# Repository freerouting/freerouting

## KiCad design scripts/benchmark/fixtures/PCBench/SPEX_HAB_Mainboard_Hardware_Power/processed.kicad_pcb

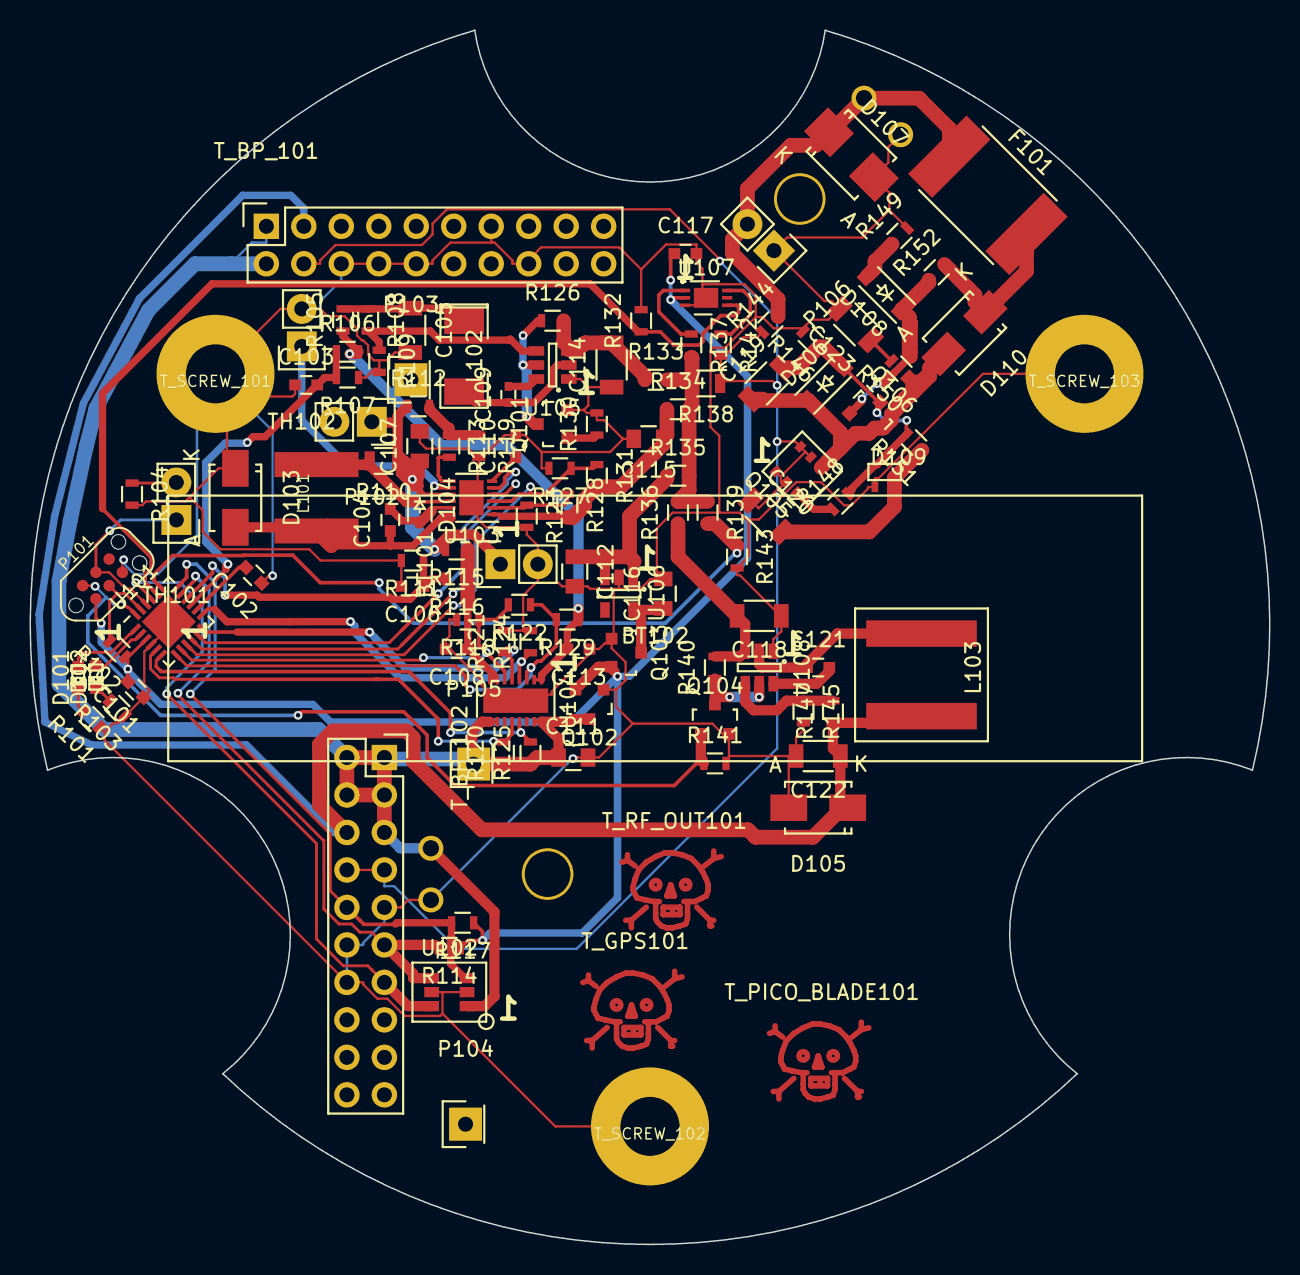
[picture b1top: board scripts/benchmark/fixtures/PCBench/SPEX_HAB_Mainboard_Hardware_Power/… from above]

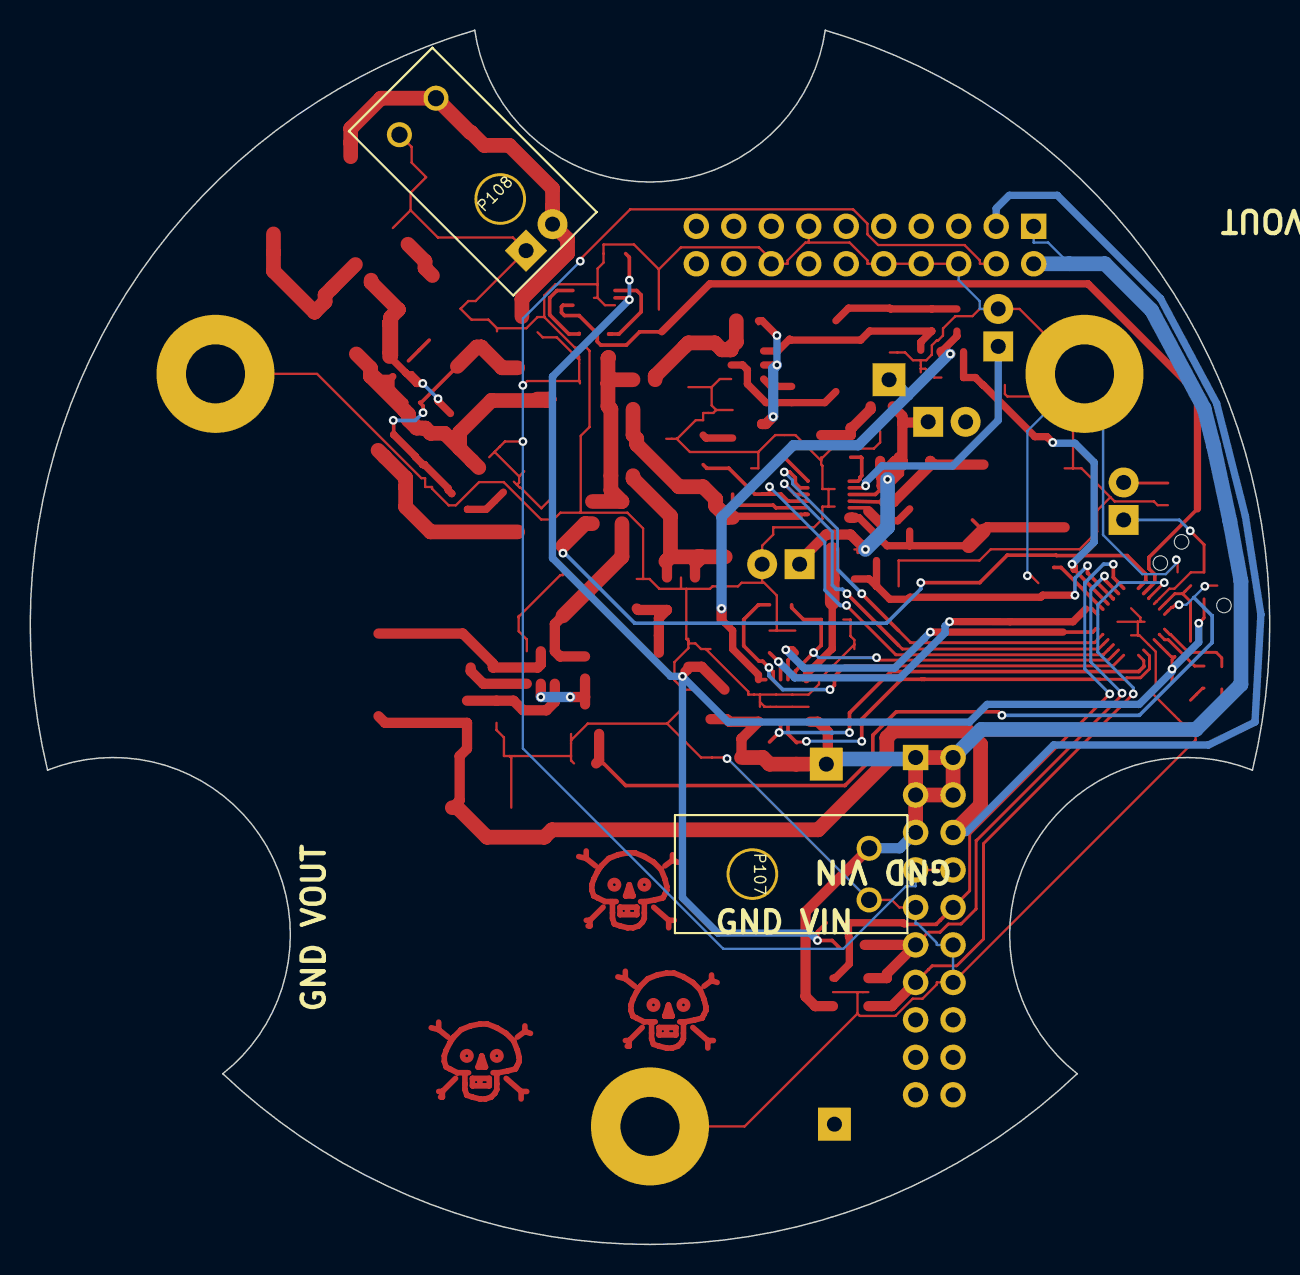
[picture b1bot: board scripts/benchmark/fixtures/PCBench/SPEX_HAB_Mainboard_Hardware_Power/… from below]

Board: 2 copper layers, 84.0 x 82.3 mm, 123 parts (2 on the bottom side), 68 nets.

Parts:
BT101: BATTERY; Pin_Header_Straight_1x02
BT102: 18650Outline; 18650
C101, C102, C104, C117: 1uf; C_0603
C103, C106: DNP; C_0603
C105, C122: 47uf; C_1206
C107, C115, C116: 10uf; C_0805
C108, C113: 1u; C_0603
C109: 100nf; C_0402
C110: .68uf; C_0603
C111: 4.7uf; C_0805
C112: 10u; C_0805
C114, C118: 22uf; C_1206
C119, C123: 1uf 100v; C_1206
C120: .1uf 100v; C_1206
C121: 100nf; C_0603
D101, D102: LED; LED-0603
D103: CMSH3-40MA; Diode-SMA_Standard
D104: CMDSH2-4L; SOD-323
D105: ZENER; Diode-SMA_Standard
D106, D108: ZENER; SOD-123
D107: ZENER; Diode-SMB_Standard
D109: D_Schottky_x2_Serial_AKC; sc70
D110: DIODE; Diode-SMA_Standard
F101: FUSE; Fuse_SMD2920
L101: 5.6uh; ASPI-6045S-5R6M-T
L102: 2.2uh; SMD-2010_Pol
L103: 3.3uh; NRS8030T3R3MJGJ
P101: TC2030-CTX; TC2030-NL_SMALL
P102: BAT_POS; Socket_Strip_Straight_1x02
P103: 3v3Out; Socket_Strip_Straight_1x01
P104: BAT_NEG; Socket_Strip_Straight_1x01
P105: 3v3Bypass; Socket_Strip_Straight_1x01
P106: 12Vin; Pin_Header_Straight_1x02
P107: 3v3Vout; ultraFitCONN_2
P108: 12Vin2; ultraFitCONN_2
Q101, Q104: MOS_N_numbered; SOT-23
Q102, Q103: Q_PMOS_GSD; SOT-23
Q105: Si3407DV
Q106: Q_PNP_BEC; SOT-23
R101, R103: 80; R_0603
R102, R143: 10000; R_0603
R104: 1500; R_0603
R105, R115, R133, R134, R135, R136: 0; R_0603
R106, R116: 3.9K; R_0603
R107, R111: 1K; R_0603
R108, R146: 33.2k; R_0603
R109, R123, R127, R145: 10k; R_0603
R110: 0.1; R_0805
R112: 14.3k; R_0603
R113: 237k; R_0603
R114, R117: 4.7k; R_0603
R118: 95.3K; R_0603
R119: 330k; R_0603
R120, R125: 470K; R_0603
R121, R124: 165; R_0603
R122: 30.1K; R_0603
R126, R130, R140, R141: 10K; R_0603
R128: 13.7k; R_0603
R129: 237K; R_0603
R131: 49.9K; R_0603
R132: 1000; R_0603
R137, R142: 100; R_0603
R138: 0.02; R_0805
R139: 200000; R_0603
R144: DNP; R_0603
R147: 56.2k; R_0603
R148, R150: 10; R_0603
R149: 27.4k; R_0603
R151: 10.2k; R_0603
R152: 100k; R_0603
TH101, TH102: THERMISTOR; Pin_Header_Straight_1x02
T_BP_101, T_BP_102: CONN_02X10; Socket_Strip_Straight_2x10
T_GPS101: SMA; Symbol_Danger_CopperTop_Small
T_PICO_BLADE101: CONN_01X08; Symbol_Danger_CopperTop_Small
T_RF_OUT101: SMA; Symbol_Danger_CopperTop_Small
T_SCREW_101, T_SCREW_102, T_SCREW_103: CONN_01X01; mounting_screw
U101: KL03-QFN24; QFN-24-1EP_4x4mm_Pitch0.5mm
U102: MMQA; SC-74
U103: LT3652; DFN-12-1EP_3x3mm_Pitch0.45mm
U104: LT4415; DFN-16-1EP_3x5mm_Pitch0.5mm
U105, U108: TPS563200; SOT-23-6
U106: TLV71209DBV; SOT-23-5
U107: LT6105

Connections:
/12Vto3v3/En: Q101.1, R130.1
/12Vto3v3/Vin: C114.2, R126.2, R133.1, U105.3
/12Vto3v3/Vout: C105.1, L102.1, R105.2, R108.1
/12Vto5V/En: P101.2, Q104.1, R141.1, U101.24
/12Vto5V/Vin: C118.2, R136.1, R140.2, U108.3
/BatVOut: C106.1, R111.1, R116.2, U101.16
/MainCurrent: R132.1, U101.20, U107.4
/SWD_CLK: P101.4, TH101.1, U101.22
/SWD_RST: P101.3, R102.2, U101.23
/SwitchVOut: C103.2, R106.1, R107.2, U101.15
/VBackup: C101.2, C117.1, P101.1, Q102.2, Q103.2, R102.1, R114.1, R117.1, U101.3, U107.2
/VInSense: R139.2, R143.1, U101.19
/VREF: C102.2, U101.14
/dualIdealDiode/Current1: R124.1, U101.13, U104.4
/dualIdealDiode/Current2: R121.1, U101.12, U104.5
/dualIdealDiode/EN1: R122.1, R129.2, U101.7, U104.3
/dualIdealDiode/EN2: R118.1, R122.2, U101.8, U104.6
/dualIdealDiode/VIN1: C113.2, P103.1, R105.1, R106.2, R129.1, U104.1, U104.2
/dualIdealDiode/VIN2: C108.1, R115.1, R116.1, U104.7, U104.8
/dualIdealDiode/WARN1: R125.2, U101.6, U104.13
/dualIdealDiode/WARN2: R120.2, U101.5, U104.12
/lifepo4Charger/CHRG: U101.10, U103.4
/lifepo4Charger/FAULT: U101.11, U103.5
/lifepo4Charger/SHDN: R127.1, R131.1, U101.9, U103.3
/lifepo4Charger/Vin: C115.1, R128.2, R131.2, R134.1, U103.1
/lifepo4Charger/Vout: BT101.1, C107.1, D104.1, P102.1, R110.1, R112.1, R115.2, U103.9
/protection/Vin: D107.1, F101.1, P106.2, P108.2, R144.2
/template/3v3: C111.1, P105.1, P107.1, Q102.3, R120.1, R125.1, T_BP_101.1, T_BP_101.2, T_BP_102.1, T_BP_102.2, T_BP_102.3, T_BP_102.4, T_BP_102.5, U102.1, U104.9, U104.10, U104.15, U104.16
/template/5v: C122.1, D105.1, L103.1, R147.1, T_BP_101.3, T_BP_102.6
/template/PSU_IRQ: T_BP_102.13, U101.21, U102.6
/template/PSU_SCL: R114.2, T_BP_102.11, U101.17, U102.4
/template/PSU_SDA: R117.2, T_BP_102.10, U101.18, U102.3
/template/VBUS: C120.1, Q105.1, Q105.2, Q105.5, Q105.6, R138.1, R142.2, R144.1, T_BP_101.4, T_BP_102.7, T_BP_102.8
GND: BT101.2, C101.1, C102.1, C103.1, C105.2, C106.2, C107.2, C108.2, C110.2, C111.2, C112.2, C113.1, C114.1, C115.2, C116.2, C117.2, C118.1, C122.2, C123.2, D103.1, D105.2, D107.2, D109.1, P101.5, P106.1, P107.2, P108.1, Q101.2, Q102.1, Q103.1, Q104.2, R101.1, R103.1, R104.2, R107.1, R109.2, R111.2, R118.2, R119.2, R121.2, R123.2, R124.2, R127.2, R130.2, R132.2, R141.2, R143.2, R145.2, R146.2, R149.2, TH102.2, T_BP_101.6, T_BP_101.8, T_BP_101.10, T_BP_101.13, T_BP_101.16, T_BP_102.9, T_BP_102.12, T_BP_102.14, T_SCREW_101.1, T_SCREW_102.1, T_SCREW_103.1, U101.4, U101.25, U102.2, U102.5, U103.13, U104.17, U105.1, U106.2, U107.3, U107.7, U108.1
unnamed: C123.1, R150.2
unnamed: C112.1, R135.1, U106.1, U106.3
unnamed: C116.1, Q103.3, U106.5
unnamed: C109.1, L102.2, U105.2
unnamed: C109.2, U105.6
unnamed: C110.1, U103.6
unnamed: C104.1, D103.2, L101.1, U103.12
unnamed: C104.2, D104.2, U103.11
unnamed: C119.1, D106.1, D110.2, Q105.4, Q106.2, R150.1
unnamed: C119.2, D106.2, D109.3, Q106.3, R146.1, R148.2, R151.2
unnamed: C120.2, D109.2, R151.1
unnamed: C121.1, L103.2, U108.2
unnamed: C121.2, U108.6
unnamed: D110.1, F101.2, R152.2
unnamed: D108.1, Q106.1, R152.1
unnamed: D108.2, R149.1
unnamed: D102.1, R103.2
unnamed: D102.2, U101.2
unnamed: D101.1, R101.2
unnamed: D101.2, U101.1
unnamed: L101.2, R110.2, U103.10
unnamed: Q105.3, R148.1
unnamed: Q101.3, R126.1, U105.5
unnamed: Q104.3, R140.1, U108.5
unnamed: R104.1, TH101.2
unnamed: R142.1, U107.6
unnamed: R137.1, U107.1
unnamed: R133.2, R134.2, R135.2, R136.2, R137.2, R138.2, R139.1
unnamed: R108.2, R109.1, U105.4
unnamed: R123.1, R128.1, U103.2
unnamed: R112.2, R113.1, R119.1
unnamed: R113.2, U103.7
unnamed: R145.1, R147.2, U108.4
unnamed: TH102.1, U103.8

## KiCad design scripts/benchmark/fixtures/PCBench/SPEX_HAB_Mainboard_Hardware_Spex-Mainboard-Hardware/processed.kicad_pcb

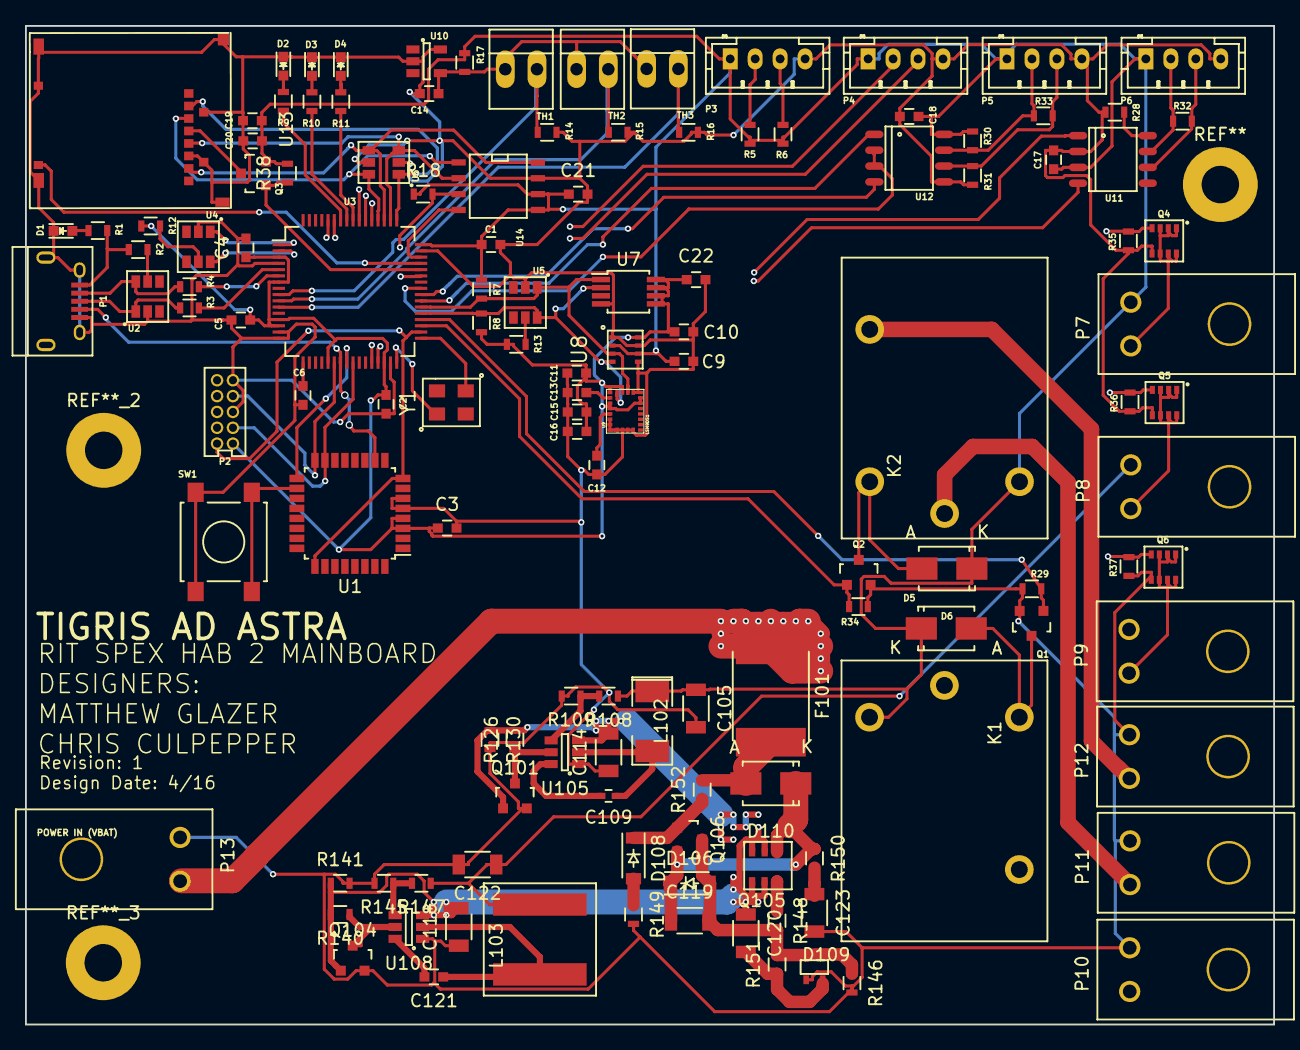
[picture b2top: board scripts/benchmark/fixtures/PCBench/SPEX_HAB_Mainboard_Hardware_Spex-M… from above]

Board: 4 copper layers, 100.0 x 80.0 mm, 131 parts (0 on the bottom side), 89 nets.

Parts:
C1, C2, C3, C4: 1uF; C_0603
C5: 2.2uF; C_0603
C6, C19: .1uF; C_0603
C9, C10, C17, C18, C21, C22: C; C_0603
C11, C13, C15: 100nF; C_0603
C12: 10nF; C_0603
C14: 4.7uF; C_0603
C16, C20: 10uF; C_0603
C105, C122: 47uf; C_1206
C109: 100nf; C_0402
C114, C118: 22uf; C_1206
C119, C123: 1uf 100v; C_1206
C120: .1uf 100v; C_1206
C121: 100nf; C_0603
D1, D2, D3, D4: LED; LED_0603
D5, D6: FM5819-W; SMA_Standard
D106, D108: ZENER; SOD-123
D109: D_Schottky_x2_Serial_AKC; sc70
D110: DIODE; Diode-SMA_Standard
F101: FUSE; Fuse_SMD2920
K1, K2: G5LE_1A4_DC3; G5LE-1A4-DC3
L102: 2.2uh; SMD-2010_Pol
L103: 3.3uh; NRS8030T3R3MJGJ
P1: USB_OTG; USB_Micro-B
P2: SWD Header; SWD-10
P3, P4, P5, P6: CONN_01X04; JST_PH_B4B-PH-K_04x2.00mm_Straight
P7, P8, P9, P10, P11, P12, P13: CONN_01X02; ultraFitCONN_2
Q1, Q2: 2N7002K; SOT-23
Q3: BSS215PH6327; SOT-23
Q4, Q5, Q6: Si5468DC; ChipFet-8
Q101, Q104: MOS_N_numbered; SOT-23
Q105: Si3407DV
Q106: Q_PNP_BEC; SOT-23
R1, R9, R10, R11: 1K; R_0603
R2, R12, R18, R29, R34, R38, R126, R130, R140, R141: 10K; R_0603
R3, R4: 33; R_0603
R5, R6, R7, R8: 4.7K; R_0603
R13, R30, R31, R35, R36, R37, R109, R145: 10k; R_0603
R14, R15, R16: 12k; R_0603
R17, R28: R; R_0603
R32, R33: 120; R_0603
R108, R146: 33.2k; R_0603
R147: 56.2k; R_0603
R148, R150: 10; R_0603
R149: 27.4k; R_0603
R151: 10.2k; R_0603
R152: 100k; R_0603
SW1: SW_PUSH; SW_SPST_B3S-1000
TH1, TH2, TH3: THERMISTOR; PINHEAD1-2
U1: MKL04Z32VLC4; LQFP-32_7x7mm_Pitch0.8mm
U2, U4, U5: NUP2201MR6; TSOP-6
U3: MK20DX256VLH7; LQFP-64_10x10mm_Pitch0.5mm
U6: MMQA6V2T1G; TSOP-6
U7: MCP9808T; MSOP-8_3x3mm_Pitch0.65mm
U8: BME280; LGA-8
U9: LSM9DS1; LGA-24
U10: LM4030; SOT-23-5
U11: MCP2551-I/SN; SO-8
U12: ST1480ABDR; SO-8
U13: SCHA4B0419; SCH4B0419
U14: AT45DB641E; SOIC-8-N
U105, U108: TPS563200; SOT-23-6
Y1: Crystal; CX3225GB16000D0HPQCC

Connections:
3.3V_MOS_CTRL: Q4.4, R35.2, U3.55
5V_MOS_CTRL: Q5.4, R36.2, U3.54
+3V3: C1.1, C2.1, C3.1, C4.1, C5.1, C9.1, C10.1, C11.1, C15.1, C16.1, C17.1, C18.1, C19.1, C20.1, C21.1, C22.1, C105.1, D5.1, D6.1, K1.4, K2.4, L102.1, P2.1, P3.1, P4.1, P5.1, P6.1, P7.2, Q3.2, R5.2, R6.2, R7.2, R8.2, R12.1, R13.1, R17.1, R18.1, R30.1, R38.2, R108.1, U1.3, U1.4, U3.3, U3.7, U3.13, U3.14, U3.21, U3.30, U3.48, U7.5, U7.6, U7.7, U7.8, U8.2, U8.6, U8.8, U9.1, U9.3, U9.7, U9.8, U9.22, U9.23, U11.3, U12.8, U14.5, U14.6
+5V: C122.1, L103.1, P8.2, R147.1
/Data_Input_Output/3.3V_MOS_OUT: P7.1, Q4.1, Q4.2, Q4.3, Q4.6, Q4.7, Q4.8
/Data_Input_Output/5V_MOS_OUT: P8.1, Q5.1, Q5.2, Q5.3, Q5.6, Q5.7, Q5.8
/Data_Input_Output/Battery_Out: K1.3, P10.1
/Data_Input_Output/CANH_out: P6.2, R32.1, U11.7
/Data_Input_Output/CANL_out: P6.3, R32.2, U11.6
/Data_Input_Output/RS485_A: P5.3, R31.1, R33.2, U12.6
/Data_Input_Output/RS485_B: P5.2, R30.2, R33.1, U12.7
/Data_Input_Output/User_In: K2.1, P11.1
/Data_Input_Output/User_Out: K2.3, P12.1
/Data_Input_Output/Vbus_MOS_OUT: P9.1, Q6.1, Q6.2, Q6.3, Q6.6, Q6.7, Q6.8
/HAB Sensors/2.5VRefVoltage: C14.1, R17.2, TH1.1, TH2.1, TH3.1, U10.4
/PTA6: P1.4, U1.10, U3.23
/PTA7: P2.2, U1.15, U3.25
/PTB0: P2.4, U1.16, U3.22
/PTB1: U1.17, U3.24
/PTB2: SW1.1, U1.18
CAN0_RX: U3.29, U11.4
CAN0_TX: U3.28, U11.1
Flash_Reset: R18.2, U3.43, U14.3
GND: C1.2, C2.2, C3.2, C4.2, C5.2, C6.2, C9.2, C10.2, C11.2, C12.2, C13.2, C14.2, C15.2, C16.2, C17.2, C18.2, C19.2, C20.2, C21.2, C22.2, C105.2, C114.1, C118.1, C122.2, C123.2, D1.1, D2.1, D3.1, D4.1, D109.1, P1.5, P1.6, P2.3, P2.5, P3.4, P4.4, P5.4, P6.4, P10.2, P11.2, P12.2, P13.1, Q1.2, Q2.2, Q4.5, Q5.5, Q6.5, Q101.2, Q104.2, R14.2, R15.2, R16.2, R28.2, R29.2, R31.2, R34.2, R35.1, R36.1, R37.1, R109.2, R130.2, R141.2, R145.2, R146.2, R149.2, SW1.2, U1.5, U1.6, U2.2, U3.4, U3.15, U3.16, U3.31, U3.47, U4.2, U5.2, U6.2, U6.5, U7.4, U8.1, U8.5, U8.7, U9.5, U9.6, U9.14, U9.15, U9.16, U9.17, U9.18, U9.19, U9.20, U10.2, U10.5, U11.2, U12.5, U13.6, U13.10, U14.7, U105.1, U108.1
I2C0_SCL: R8.1, U3.37, U5.6, U7.2, U8.4, U9.2
I2C0_SDA: R7.1, U3.38, U5.1, U7.1, U8.3, U9.4
I2C1_SCL: P3.3, R6.1, U3.2, U4.6
I2C1_SDA: P3.2, R5.1, U3.1, U4.1
LED_Heartbeat: R9.1, U3.58
LED_Status_1: R10.1, U3.57
LED_Status_2: R11.1, U3.56
unnamed: C6.1, U3.17
unnamed: C12.1, U9.21
unnamed: C13.1, U9.24
unnamed: C109.1, L102.2, U105.2
unnamed: C109.2, U105.6
unnamed: C119.1, D106.1, D110.1, Q105.4, Q106.2, R150.1
unnamed: C119.2, D106.2, D109.3, Q106.3, R146.1, R148.2, R151.2
unnamed: C120.2, D109.2, R151.1
unnamed: C121.1, L103.2, U108.2
unnamed: C121.2, U108.6
unnamed: C123.1, R150.2
unnamed: D1.2, R1.2
unnamed: D2.2, R9.2
unnamed: D3.2, R10.2
unnamed: D4.2, R11.2
unnamed: D5.2, K1.2, Q1.3
unnamed: D6.2, K2.2, Q2.3
unnamed: D108.1, Q106.1, R152.1
unnamed: D108.2, R149.1
unnamed: D110.2, F101.2, R152.2
unnamed: P1.1, R1.1, R2.2
unnamed: P1.2, R4.2, U2.6
unnamed: P1.3, R3.2, U2.1
unnamed: Q3.3, U13.4
unnamed: Q101.3, R126.1, U105.5
unnamed: Q104.3, R140.1, U108.5
unnamed: Q105.3, R148.1
unnamed: R2.1, U2.5
unnamed: R3.1, U3.5
unnamed: R4.1, U3.6
unnamed: R12.2, U4.5
unnamed: R13.2, U5.5
unnamed: R28.1, U11.8
unnamed: R108.2, R109.1, U105.4
unnamed: R145.1, R147.2, U108.4
unnamed: U3.32, Y1.1
unnamed: U3.33, Y1.2
RESET_b: P2.10, U1.8, U1.25, U3.34
RX/TX_CTRL: U3.41, U12.2, U12.3
Relay1_ctrl: Q1.1, R29.1, U3.36
Relay2_ctrl: Q2.1, R34.1, U3.35
SD_CTRL: Q3.1, R38.1, U3.44
SD_Detect: U3.45, U13.9
SPI0_CS0: U3.49, U6.1, U13.2
SPI0_CS1: U3.46, U14.4
SPI0_MISO: U3.51, U6.4, U13.7, U14.8
SPI0_MOSI: U3.52, U6.6, U13.3, U14.1
SPI0_SCK: U3.50, U6.3, U13.5, U14.2
Temp1: R14.1, TH1.2, U3.9
Temp2: R15.1, TH2.2, U3.10
Temp3: R16.1, TH3.2, U3.11
UART0_RX: U3.39, U12.1
UART0_TX: U3.40, U12.4
UART2_RX: P4.3, U3.59
UART2_TX: P4.2, U3.60
VBatt: F101.1, K1.1, P13.2
Vbus: C114.2, C118.2, C120.1, P9.2, Q101.1, Q104.1, Q105.1, Q105.2, Q105.5, Q105.6, R126.2, R130.1, R140.2, R141.1, U105.3, U108.3
Vbus_MOS_CTRL: Q6.4, R37.2, U3.53
